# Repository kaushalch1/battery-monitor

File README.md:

# CellCheck 

CellCheck is a battery discharge analyzer designed to measure battery voltage, current, power, temperature, estimated capacity, energy, and approximate internal resistance.

the planned hardware supports interchangeable holders for single 18650 Li ion cells and AA/AAA NiMH/NiCd cells. It uses an esp32-s3 controller, an oled dashboard, usb serial communication, and a protected programmable electronic load.

## Features

- battery voltage, current, power, and temperature monitoring
- SSD1306 OLED dashboard
- usb serial telemetry for PC monitoring and CSV logging
- start, stop, and batterymchemistry selection buttons
- capacity calculation in mAh
- energy calculation in Wh
- planned programmable discharge load with independent hardware shutdown
- planned support for interchangeable 18650 and AA/AAA battery holders

## PCB Setup

- collect all components according to the BOM.
- solder the components onto the pcb, starting with small SMD components and then larger parts and connectors.
- check solder joints and use a multimeter to check for short circuits.
- power the logic section using a current limited power supply and verify the 3.3v rail.
- upload the firmware to the esp32-s3.
- test the oled, buttons, LEDs, voltage sensing, and temperature sensing.
- calibrate voltage and current readings using known references.
- test the electronic load and hardware safety cutoffs with a suitable dummy load before connecting a battery.

# Battery Monitor — Bill of Materials

| Name | Purpose | Quantity | Total Cost (USD) | Link | Distributor |
|---|---|---:|---:|---|---|
| ESP32-S3-WROOM-1 (N16R8 assumed) | Main MCU (Wi-Fi/BLE) | 1 | 5.54 | [Link](https://www.lcsc.com/product-detail/C2913202.html) | LCSC |
| MCP9808T-E/MC (DFN-8) | Digital temperature sensor | 1 | 2.55 | [Link](https://www.lcsc.com/product-detail/C194710.html) | LCSC |
| 0.91 inch OLED (ER-OLEDM0.91-1W-I2C) | Display | 1 | 2.80 | [Link](https://www.buydisplay.com/i2c-white-0-91-inch-oled-display-module-128x32-arduino-raspberry-pi) | BuyDisplay |
| TPS63020DSJR | Buck-boost converter | 1 | 0.91 | [Link](https://www.lcsc.com/product-detail/C15483.html) | LCSC |
| INA226AIDGSR | Voltage/current/power monitor | 1 | 0.65 | [Link](https://www.lcsc.com/product-detail/C49851.html) | LCSC |
| 18650 holder (BH-18650-A1AJ006) | 18650 cell holder | 1 | 0.49 | [Link](https://www.lcsc.com/product-detail/C5290175.html) | LCSC |
| AA holder (BH-AA-A5BJ012) | AA cell holder | 1 | 0.46 | [Link](https://www.lcsc.com/product-detail/C5290180.html) | LCSC |
| NMOS TO-252 (Q2, Q3) | Load/discharge switching MOSFETs | 2 | 0.40 | [Link](https://www.lcsc.com/search?q=NMOS+TO-252) | LCSC |
| SMD tact switch (EVP-BF type, SW4-SW6) | User buttons | 3 | 0.45 | [Link](https://www.lcsc.com/search?q=EVPBF+tactile+switch) | LCSC |
| LM397 comparator (HGSEMI LM397M5/TR, SOT-23-5) | Comparator | 1 | 0.31 | [Link](https://www.lcsc.com/product-detail/C910849.html) | LCSC |
| DPDT slide switch (JS202011JCQN) | Mode/power switch SW3 | 1 | 0.25 | [Link](https://www.lcsc.com/search?q=JS202011JCQN) | LCSC |
| USB-C receptacle (TYPE-C-31-M-12) | USB-C port | 1 | 0.19 | [Link](https://www.lcsc.com/product-detail/C165948.html) | LCSC |
| USBLC6-2SC6 | USB ESD protection | 1 | 0.13 | [Link](https://www.lcsc.com/product-detail/C7519.html) | LCSC |
| 1.5uH inductor (Sunlord MWSA0402S) | Buck-boost inductor | 1 | 0.10 | [Link](https://www.lcsc.com/search?q=MWSA0402S-1R5) | LCSC |
| LM358 (SOIC-8) | Dual op-amp | 1 | 0.10 | [Link](https://www.lcsc.com/search?q=LM358+SOIC-8) | LCSC |
| JST XH 2-pin header (J2, J3) | Connectors | 2 | 0.08 | [Link](https://www.lcsc.com/search?q=B2B-XH-A) | LCSC |
| Tact switch 6mm THT (SW1, SW2) | User buttons | 2 | 0.07 | [Link](https://www.lcsc.com/search?q=tactile+switch+6x6+THT) | LCSC |
| PMOS SOT-23 (Q1) | Reverse-polarity/power switch | 1 | 0.05 | [Link](https://www.lcsc.com/search?q=PMOS+SOT-23) | LCSC |
| JST XH 4-pin header (B4B-XH-A) | Sensor/expansion connector | 1 | 0.05 | [Link](https://www.lcsc.com/product-detail/C144395.html) | LCSC |
| Fuse 1206 | Overcurrent protection | 1 | 0.05 | [Link](https://www.lcsc.com/search?q=1206+fuse) | LCSC |
| NTC 10k 0805 | Temperature sensing thermistor | 1 | 0.04 | [Link](https://www.lcsc.com/search?q=10k+NTC+0805) | LCSC |
| LED 0603 | Status LEDs | 2 | 0.04 | [Link](https://www.lcsc.com/search?q=0603+LED) | LCSC |
| 10uF capacitor 0603 | Bulk/decoupling capacitors | 3 | 0.04 | [Link](https://www.lcsc.com/search?q=10uF+0603+MLCC) | LCSC |
| 100nF capacitor 0603 | IC bypass capacitors | 3 | 0.01 | [Link](https://www.lcsc.com/search?q=100nF+0603+MLCC) | LCSC |
| Resistors 0603 (0.02, 0.22, 220, 1k, 2.4k, 4.7k, 5.1k, 10k, 100k) | Dividers, pull-ups, current sense | 21 | 0.14 | [Link](https://www.lcsc.com/search?q=0603+1%25+resistor) | LCSC |
| PCB (bare boards, JLCPCB minimum order of 5) | Main PCBs | 5 | 2.00 | [Link](https://jlcpcb.com/) | JLCPCB |
| PCB assembly (PCBA setup + stencil + fees, 1-board order) | SMT + through-hole assembly fees | 1 | 7.00 | [Link](https://jlcpcb.com/) | JLCPCB |

# schematic:

# pcb:

# 3d view:

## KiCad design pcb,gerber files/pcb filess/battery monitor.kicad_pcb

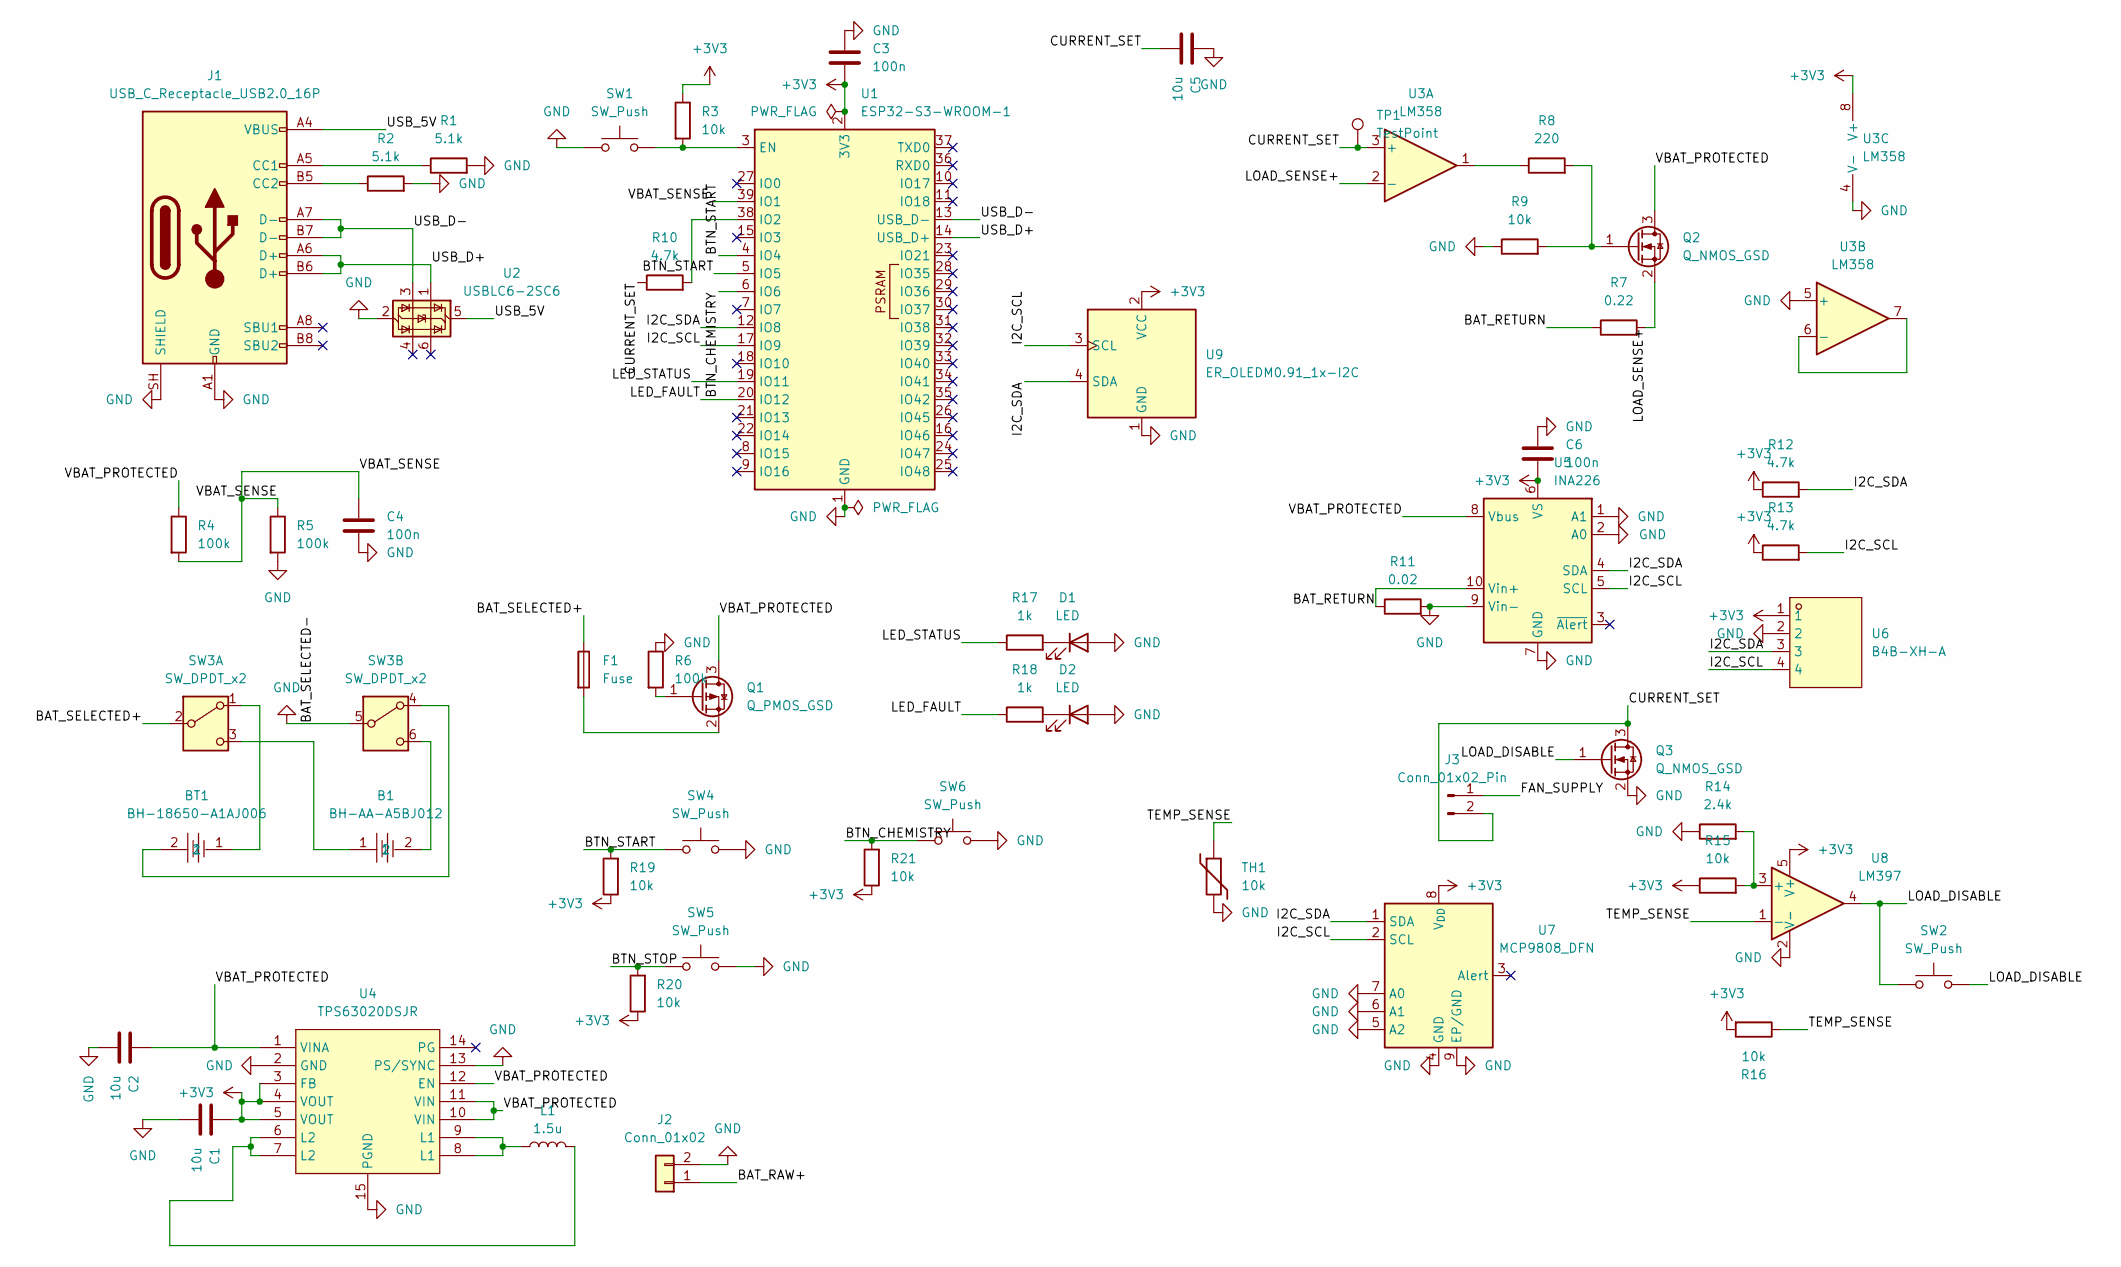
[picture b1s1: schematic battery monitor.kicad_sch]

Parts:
B1: BH-AA-A5BJ012; BAT-TH_BH-AA-A5BJ012; MPN BH-AA-A5BJ012; LCSC Part C5290180
BT1: BH-18650-A1AJ006; BAT-TH_BH-18650-A1AJ006; MPN BH-18650-A1AJ006; LCSC Part C5290175
C1, C2, C5: 10u; C_0603_1608Metric
C3, C4, C6: 100n; C_0603_1608Metric
D1, D2: LED; LED_0603_1608Metric
F1: Fuse; Fuse_1206_3216Metric
J1: USB_C_Receptacle_USB2.0_16P; USB_C_Receptacle_HRO_TYPE-C-31-M-12
J2: Conn_01x02; JST_XH_B2B-XH-A_1x02_P2.50mm_Vertical
J3: Conn_01x02_Pin; JST_XH_B2B-XH-A_1x02_P2.50mm_Vertical
L1: 1.5u; L_Sunlord_MWSA0402S
Q1: Q_PMOS_GSD; SOT-23
Q2, Q3: Q_NMOS_GSD; TO-252-2
R1, R2: 5.1k; R_0603_1608Metric
R3, R9, R15, R16, R19, R20, R21: 10k; R_0603_1608Metric
R4, R5, R6: 100k; R_0603_1608Metric
R7: 0.22; R_0603_1608Metric
R8: 220; R_0603_1608Metric
R10, R12, R13: 4.7k; R_0603_1608Metric
R11: 0.02; R_0603_1608Metric
R14: 2.4k; R_0603_1608Metric
R17, R18: 1k; R_0603_1608Metric
SW1, SW2: SW_Push; SW_PUSH_6mm
SW3: SW_DPDT_x2; SW_DPDT_CK_JS202011JCQN
SW4, SW5, SW6: SW_Push; SW_SPST_EVPBF
TH1: 10k; R_0805_2012Metric
TP1: TestPoint; TestPoint_Pad_D1.0mm
U1: ESP32-S3-WROOM-1
U2: USBLC6-2SC6; SOT-23-6
U3: LM358; SOIC-8_3.9x4.9mm_P1.27mm
U4: TPS63020DSJR; VSON-14_L4.0-W3.0-P0.50-BL-EP_TI_DSJ; MPN TPS63020DSJR; LCSC Part C15483
U5: INA226; TSSOP-10_3x3mm_P0.5mm
U6: B4B-XH-A; CONN-TH_B4B-XH-A-LF-SN; MPN B4B-XH-A(LF)(SN); LCSC Part C144395
U7: MCP9808_DFN; DFN-8-1EP_3x2mm_P0.5mm_EP1.7x1.4mm
U8: LM397; SOT-23-5
U9: ER_OLEDM0.91_1x-I2C

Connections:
+3V3: C1.1, C3.2, C6.2, R3.1, R12.1, R13.1, R15.1, R16.2, R19.1, R20.1, R21.1, U1.2 (3V3), U3.8 (V+), U4.3 (FB), U4.4 (VOUT), U4.5 (VOUT), U5.6 (VS), U6.1, U7.8 (V_{DD}), U8.5 (V+), U9.2 (VCC)
/BAT_RAW+: J2.1
/BAT_RETURN: R7.1, R11.1, U5.10 (Vin+)
/BAT_SELECTED+: F1.1, SW3.2 (B)
/BTN_CHEMISTRY: R21.2, SW6.1, U1.6 (IO6)
/BTN_START: R19.2, SW4.1, U1.4 (IO4), U1.5 (IO5)
/BTN_STOP: R20.2, SW5.1
/CURRENT_SET: C5.2, J3.2, Q3.3 (D), R10.1, TP1.1 (1_1), U3.3 (+)
/FAN_SUPPLY: J3.1
/I2C_SCL: R13.2, U1.17 (IO9), U5.5 (SCL), U6.4, U7.2 (SCL), U9.3 (SCL)
/I2C_SDA: R12.2, U1.12 (IO8), U5.4 (SDA), U6.3, U7.1 (SDA), U9.4 (SDA)
/LED_FAULT: R18.1, U1.20 (IO12)
/LED_STATUS: R17.1, U1.19 (IO11)
/LOAD_DISABLE: Q3.1 (G), SW2.1, SW2.2, U8.4
/LOAD_SENSE+: Q2.2 (S), R7.2, U3.2 (-)
/TEMP_SENSE: R16.1, TH1.1, U8.1 (-)
/USB_5V: J1.A4 (VBUS), J1.A9 (VBUS), J1.B4 (VBUS), J1.B9 (VBUS), U2.5 (VBUS)
/USB_D+: J1.A6 (D+), J1.B6 (D+), U1.14 (USB_D+), U2.1 (I/O1)
/USB_D−: J1.A7 (D-), J1.B7 (D-), U1.13 (USB_D-), U2.3 (I/O2)
/VBAT_PROTECTED: C2.1, Q1.3 (D), Q2.3 (D), R4.1, U4.1 (VINA), U4.10 (VIN), U4.11 (VIN), U4.12 (EN), U5.8 (Vbus)
/VBAT_SENSE: C4.1, R4.2, R5.1, U1.39 (IO1)
GND: C1.2, C2.2, C3.1, C4.2, C5.1, C6.1, D1.2 (A), D2.2 (A), J1.A1 (GND), J1.A12 (GND), J1.B1 (GND), J1.B12 (GND), J1.SH (SHIELD), J2.2, Q3.2 (S), R1.2, R2.2, R5.2, R6.1, R9.1, R11.2, R14.1, SW1.1, SW3.5 (B), SW4.2, SW5.2, SW6.2, TH1.2, U1.1 (GND), U1.40 (GND), U1.41 (GND), U2.2 (GND), U3.4 (V-), U3.5 (+), U4.2 (GND), U4.13 (PS/SYNC), U4.15 (PGND), U5.1 (A1), U5.2 (A0), U5.7 (GND), U5.9 (Vin-), U6.2, U7.4 (GND), U7.5 (A2), U7.6 (A1), U7.7 (A0), U7.9 (EP/GND), U8.2 (V-), U9.1 (GND)
unnamed: D1.1 (K), R17.2
unnamed: D2.1 (K), R18.2
unnamed: J1.A5 (CC1), R1.1
unnamed: J1.B5 (CC2), R2.1
unnamed: L1.1, U4.8 (L1), U4.9 (L1)
unnamed: L1.2, U4.6 (L2), U4.7 (L2)
unnamed: Q1.1 (G), R6.2
unnamed: F1.2, Q1.2 (S)
unnamed: Q2.1 (G), R8.2, R9.2
unnamed: R8.1, U3.1
unnamed: BT1.1, SW3.1 (A)
unnamed: B1.1, SW3.3 (C)
unnamed: BT1.2, SW3.4 (A)
unnamed: B1.2, SW3.6 (C)
unnamed: R3.2, SW1.2, U1.3 (EN)
unnamed: R10.2, U1.38 (IO2)
unnamed: U3.6 (-), U3.7
unnamed: R14.2, R15.2, U8.3 (+)

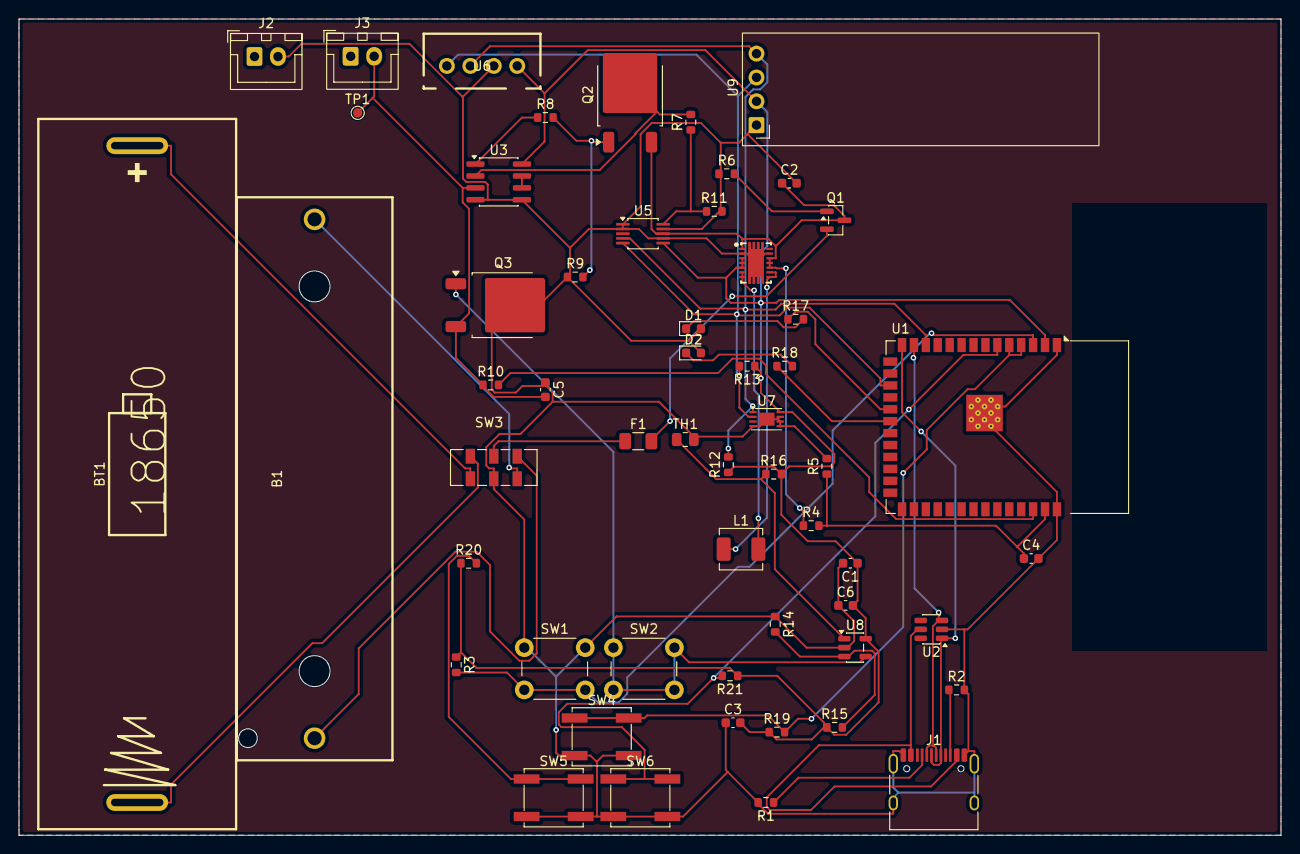
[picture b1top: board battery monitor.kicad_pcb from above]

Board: 2 copper layers, 134.5 x 87.0 mm, 56 parts (0 on the bottom side), 38 nets.
